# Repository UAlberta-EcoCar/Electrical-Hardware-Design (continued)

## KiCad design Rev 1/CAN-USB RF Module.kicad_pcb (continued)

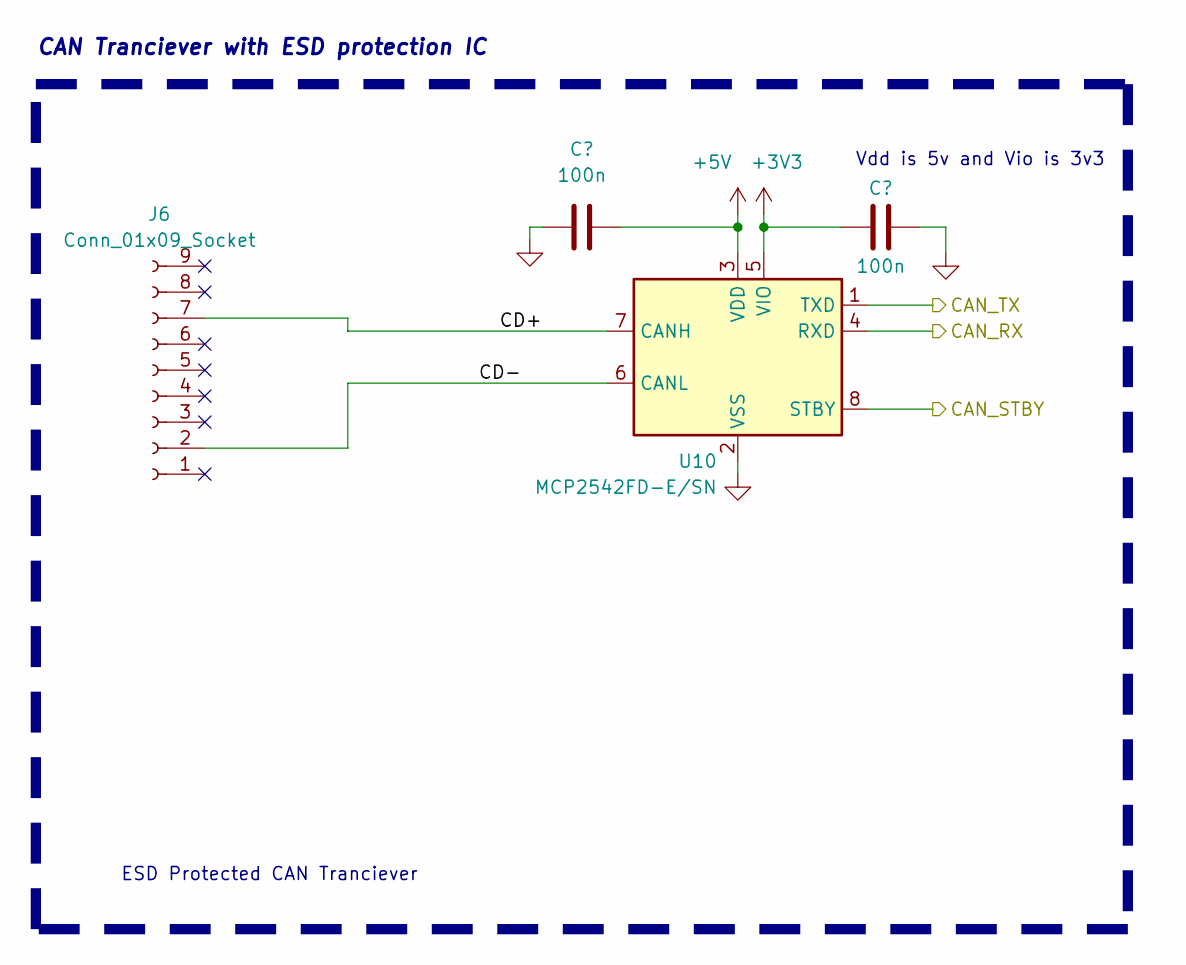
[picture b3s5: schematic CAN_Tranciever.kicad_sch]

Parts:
C45, C46: 100n; C_0603_1608Metric; LCSC # C1591
J6: Conn_01x09_Socket; DSUB-9_Female_Horizontal_P2.77x2.84mm_EdgePinOffset7.70mm_H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; LCSC # C305941
U10: MCP2542FD-E/SN; SOIC-8-1EP_3.9x4.9mm_P1.27mm_EP2.29x3mm; LCSC # C220598

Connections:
+3V3: C46.2, U10.5 (VIO); also elsewhere on the board
+5V: C45.2, U10.3 (VDD); also elsewhere on the board
/CAN Tranciever/CD+: J6.7, U10.7 (CANH)
/CAN Tranciever/CD-: J6.2, U10.6 (CANL)
/CAN_RX: U10.4 (RXD); also elsewhere on the board
/CAN_STBY: U10.8 (STBY); also elsewhere on the board
/CAN_TX: U10.1 (TXD); also elsewhere on the board
GND: C45.1, C46.1, U10.2 (VSS), U10.9 (VSS); also elsewhere on the board

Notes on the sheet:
ESD Protected CAN Tranciever
Vdd is 5v and Vio is 3v3
CAN Tranciever with ESD protection IC

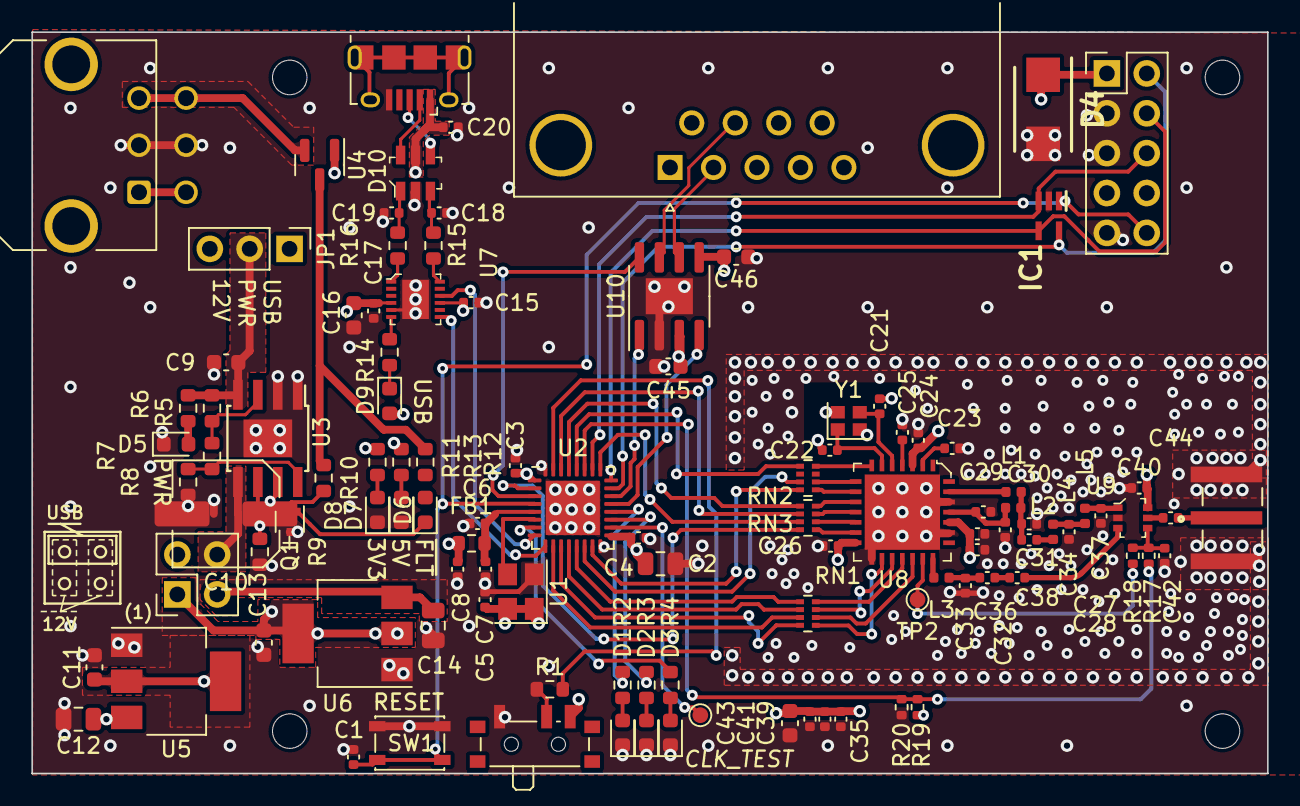
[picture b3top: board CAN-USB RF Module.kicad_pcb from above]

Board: 4 copper layers, 78.7 x 47.2 mm, 113 parts (0 on the bottom side), 91 nets.

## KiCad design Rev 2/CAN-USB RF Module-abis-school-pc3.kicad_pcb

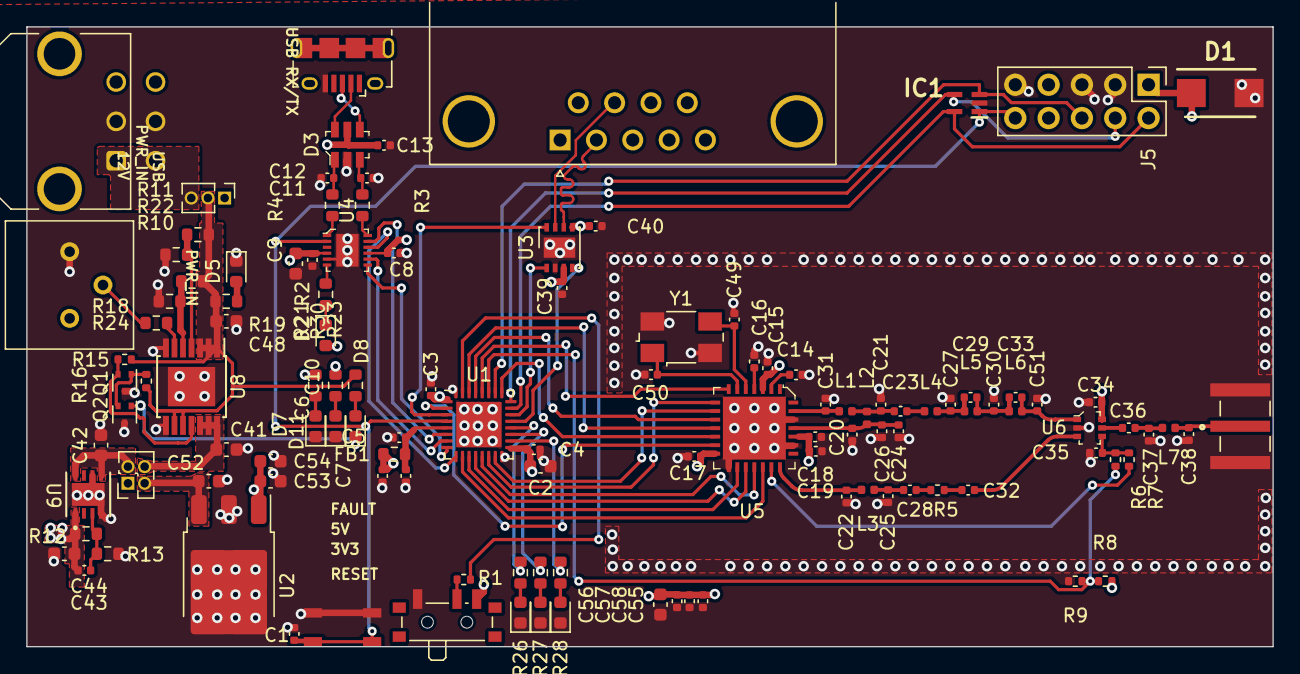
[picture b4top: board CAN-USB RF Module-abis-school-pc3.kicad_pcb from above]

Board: 4 copper layers, 95.0 x 47.2 mm, 120 parts (0 on the bottom side), 79 nets.

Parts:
C1, C3, C4, C8, C10, C13, C14, C15, C16, C17, C19, C39, C40: 100n; C_0402_1005Metric
C2, C48, C54: 10u; C_0603_1608Metric
C5, C20, C31: 10n; C_0402_1005Metric
C6, C7, C55, C57, C58: 1u; C_0402_1005Metric
C9: 4u7; C_0603_1608Metric
C11, C12, C18, C24, C26, C28, C32, C36: 47p; C_0402_1005Metric
C21: 8p2; C_0402_1005Metric
C22, C29, C33, C37, C38, C51: NC; C_0402_1005Metric
C23: 22p; C_0402_1005Metric
C25, C30: 3p3; C_0402_1005Metric
C27: 6p8; C_0402_1005Metric
C34, C35: 1n; C_0402_1005Metric
C41, C42, C52, C53: 1u; C_0603_1608Metric
C43: 10p; C_0402_1005Metric
C44: 2u2; C_0603_1608Metric
C49, C50: 8p; C_0402_1005Metric
C56: 22u; C_0603_1608Metric
D1: SMLVT3V3; DIOM5436X265N
D2: AMBER RX/TX; LED_0603_1608Metric
D3: USBLC6-2SC6; SOT23-6L
D4, D9: AMBER; LED_0603_1608Metric
D5, D7, D11: BLUE; LED_0603_1608Metric
D8: RED; LED_0603_1608Metric
D10: GREEN; LED_0603_1608Metric
FB1: 120R; R_0603_1608Metric
IC1: ESDALC6V1W5; SOT65P210X110-5N
J1: USB JMPR; PinHeader_2x02_P1.27mm_Vertical
J2: USB_B_Micro; USB_Micro-B_Amphenol_10118194_Horizontal
J3: Conn_Coaxial; TAOGLAS_EMPCB.SMAFSTJ.B.HT
J5: Conn_02x05_Top_Bottom; PinHeader_2x05_P2.54mm_Vertical
J6: Fuel Cell Connector; Molex_Micro-Fit_3.0_43045-0621_2x03-1MP_P3.00mm_Horizontal
J7: Conn_01x09_Socket; DSUB-9_Female_Horizontal_P2.77x2.84mm_EdgePinOffset7.70mm_H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
JP2: Power In; PinHeader_1x03_P1.27mm_Vertical
L1: 1n5; L_0402_1005Metric
L2: 33n; L_0402_1005Metric
L3: 10n; L_0402_1005Metric
L4, L5: 5n6; L_0402_1005Metric
L6, L7: 0H; L_0402_1005Metric
Q1, Q2: NMOS; SOT-523
R1, R15, R16: 10k; R_0402_1005Metric
R2, R21: 260R; R_0603_1608Metric
R3, R4: 27R; R_0603_1608Metric
R5: 0R; R_0402_1005Metric
R6: 100R; R_0402_1005Metric
R7, R9: NC; R_0402_1005Metric
R8: 1k; R_0402_1005Metric
R10, R11: 2M2; R_0603_1608Metric
R12: 500k; R_0603_1608Metric
R13: 160k; R_0603_1608Metric
R18: 225k; R_0603_1608Metric
R19, R23, R30: 600R; R_0603_1608Metric
R22: 800k; R_0603_1608Metric
R24, R26, R27, R28: 10k; R_0603_1608Metric
RV1: SETI; Potentiometer_Bourns_3386P_Vertical
SW1: RESET; SMD_025816_WRE
SW2: BOOT0; SW_SPDT_PCM12
U1: STM32L442KCU6; QFN-32-1EP_5x5mm_P0.5mm_EP3.45x3.45mm
U2: LP38690DTX; TO-252-3_TabPin2
U3: MCP2542FDxMF; DFN-8-1EP_3x3mm_P0.65mm_EP1.55x2.4mm
U4: FT234XD-R; DFN-12-1EP_3x3mm
U5: SX1276IMLTRT; VQFN-28-1EP_6x6mm
U6: P4259-63; SOT-363
U8: MAX14572; TSSOP-14-1EP_4.4x5mm_P0.65mm
U9: TLV76601QWDRBRQ1; TLV76601QWDRBRQ1_TEX
Y1: 32MHz; Crystal_SMD_0603-4Pin_6.0x3.5mm

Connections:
+3.3VA: C5.1, C6.1, FB1.1, U1.5 (VDDA)
+3V3: C2.1, C3.1, C4.1, C7.1, C8.1, C15.1, C17.1, C18.1, C19.1, C34.1, C40.2, C43.1, C44.1, C55.1, C56.1, C57.1, C58.1, D1.1 (K), D2.2 (A), FB1.2, J5.1, R8.2, R12.1, R21.1, SW2.3 (C), U1.1 (VDD), U1.17 (VDD), U3.5 (VIO), U4.9 (VCCIO), U5.3 (VBAT_ANA), U5.14 (VBAT_DIG), U5.24 (VBAT_RF), U6.6 (~CTRL/VDD), U9.1 (OUT)
+5V: C9.1, C10.1, C39.2, C53.1, C54.1, J1.1, R30.1, U2.1 (OUTPUT), U3.3 (VDD), U4.4 (VCC)
+12V: J6.1, J6.4, JP2.3 (B)
/BOOT0: R1.1, R1.2, SW2.2 (B), U1.31 (PH3)
/CAN Tranciever/CD+: J7.7, U3.7 (CANH)
/CAN Tranciever/CD-: J7.2, U3.6 (CANL)
/CAN_RX: U1.21 (PA11), U3.4 (RXD)
/CAN_STBY: U1.3 (PC15), U3.8 (STBY)
/CAN_TX: U1.22 (PA12), U3.1 (TXD)
/DEBUG_SWCLK: IC1.4 (I/03), J5.4, U1.24 (PA14)
/DEBUG_SWDIO: IC1.5 (I/04), J5.2, U1.23 (PA13)
/DEBUG_SWO: IC1.3 (I/02), J5.6, U1.26 (PB3)
/DIO0: U1.14 (PB0), U5.8 (DIO0)
/DIO1: U1.15 (PB1), U5.9 (DIO1/DCLK)
/DIO2: U1.29 (PB6), U5.10 (DIO2/DATA)
/DIO3: U1.30 (PB7), U5.11 (DIO3)
/DIO4: U1.25 (PA15), U5.12 (DIO4)
/DIO5: U1.2 (PC14), U5.13 (DIO5)
/LoRa Tranciever/RFI_HF: C22.1, L3.1, U5.21 (RFI_HF(GND))
/LoRa Tranciever/RFO_HF: C31.1, L1.1, U5.27 (PA_BOOST)
/LoRa Tranciever/RXTX_SW: C35.1, R6.1, R7.1, U6.4 (CTRL)
/LoRa Tranciever/RXTX_SX: R7.2, U5.20 (RXTX/RF_MOD)
/NRST: C1.2, IC1.1 (I/01), J5.10, SW1.3 (K), SW1.4 (A), U1.4 (NRST), U4.2 (RESET#)
/Power Regulator/5V: C42.1, J1.2, U9.5 (EN), U9.8 (IN)
/Power Regulator/12V: C52.1, J1.3, U2.3 (INPUT)
/Power Regulator/FB: C43.2, R12.2, R13.1, U9.3 (FB)
/Power Regulator/FUSE_IN: C48.1, JP2.2 (C), R10.1, R11.1, R15.1, R16.1, R19.1, R23.1, U8.1 (IN), U8.2 (IN), U8.3 (IN), U8.9 (RIEN), U8.10 (EN)
/Power Regulator/FUSE_OUT: C41.1, J1.4, U8.12 (OUT), U8.13 (OUT), U8.14 (OUT)
/Power Regulator/OVLO: R10.2, R18.1, U8.5 (OVLO)
/Power Regulator/SETI: R24.1, U8.6 (SETI)
/Power Regulator/UVLO: R11.2, R22.1, U8.4 (UVLO)
/Power Regulator/~FLAG: Q1.2 (G), R15.2, U8.11 (~FLAG)
/SPI1_MISO: U1.12 (PA6), U5.17 (MISO)
/SPI1_MOSI: U1.13 (PA7), U5.18 (MOSI)
/SPI1_NSS: U1.10 (PA4), U5.19 (NSS)
/SPI1_SCK: U1.11 (PA5), U5.16 (SCK)
/SW_RXTX: R6.2, R8.1, R9.2, U1.27 (PB4)
/SX_RESET: U1.28 (PB5), U5.7 (NRESET)
/UART2_USB_CTS: U1.6 (PA0), U4.11 (CTS#)
/UART2_USB_RTS: U1.7 (PA1), U4.8 (RTS#)
/UART2_USB_RX: U1.9 (PA3), U4.10 (RXD)
/UART2_USB_TX: U1.8 (PA2), U4.7 (TXD)
/USB Interface/USB_D+: C11.2, D3.3, D3.4, J2.3 (D+), R3.1, R3.2, U4.12 (USBDP)
/USB Interface/USB_D-: C12.2, D3.1, D3.6, J2.2 (D-), R4.1, R4.2, U4.1 (USBDM)
GND: C1.1, C2.2, C3.2, C4.2, C5.2, C6.2, C7.2, C8.2, C9.2, C10.2, C11.1, C12.1, C13.1, C14.2, C15.2, C16.2, C17.2, C18.2, C19.2, C20.2, C21.2, C22.2, C24.2, C25.2, C26.2, C27.1, C30.1, C31.2, C34.2, C35.2, C37.1, C38.1, C39.1, C40.1, C41.2, C42.2, C44.2, C48.2, C49.2, C50.2, C51.1, C52.2, C53.2, C54.2, C55.2, C56.2, C57.2, C58.2, D1.2 (A), D3.2, D4.1 (K), D5.1 (K), D7.1 (K), D9.1 (K), D10.1 (K), D11.1 (K), IC1.2 (GND), J2.5 (GND), J3.2 (Ext), J5.3, J5.5, J5.9, J6.2, J6.5, Q1.3 (S), Q2.3 (S), R9.1, R13.2, R18.2, R22.2, RV1.3, SW1.1, SW1.2, SW2.1 (A), U1.16 (VSS), U1.32 (VSS), U1.33 (VSS), U2.2 (GND), U3.2 (VSS), U3.9 (VSS), U4.5 (GND), U4.13 (GND), U5.15 (GND), U5.23 (GND), U5.26 (GND), U5.29 (GND), U6.2 (GND), U8.7 (GND), U8.8 (~HVEN), U8.15 (GND), U9.4 (GND), U9.6 (GND), U9.9 (GND), Y1.2, Y1.4
unnamed: C21.1, C23.1, L1.2, L2.1
unnamed: C23.2, L4.1
unnamed: C25.1, C28.1, L3.2
unnamed: C27.2, C29.2, L4.2, L5.1
unnamed: C28.2, R5.1
unnamed: C29.1, C30.2, C33.2, L5.2, L6.1
unnamed: C32.1, R5.2
unnamed: C36.2, C37.2, L7.1
unnamed: D2.1 (K), R2.2
unnamed: D4.2 (A), R28.1
unnamed: D5.2 (A), R19.2
unnamed: D7.2 (A), R21.2
unnamed: D8.2 (A), R23.2
unnamed: D8.1 (K), Q2.1 (D)
unnamed: D9.2 (A), R27.1
unnamed: D10.2 (A), R26.1
unnamed: D11.2 (A), R30.2
unnamed: C38.2, J3.1 (In), L7.2
unnamed: Q1.1 (D), Q2.2 (G), R16.2
unnamed: R24.2, RV1.2
unnamed: R28.2, U1.18 (PA8)
unnamed: R27.2, U1.19 (PA9)
unnamed: R26.2, U1.20 (PA10)
unnamed: R2.1, U4.6 (CBUS0)
unnamed: C14.1, U5.2 (VR_ANA)
unnamed: C16.1, U5.4 (VR_DIG)
unnamed: C20.1, C24.1, C26.1, L2.2, U5.25 (VR_PA)
unnamed: C49.1, U5.5 (XTA), Y1.3
unnamed: C50.1, U5.6 (XTB), Y1.1
unnamed: C33.1, C51.2, L6.2, U6.1 (RF1)
unnamed: C32.2, U6.3 (RF2)
unnamed: C36.1, U6.5 (RFC)
VBUS_UP: C13.2, D3.5, J2.1 (VBUS), JP2.1 (A)
